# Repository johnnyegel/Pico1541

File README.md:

# Pico1541

A cycle-accurate Commodore 1541 disk drive emulator running on the Raspberry Pi Pico 2 (RP2350).

Unlike high-level IEC drive emulators (such as standard SD2IEC devices), **Pico1541** provides true hardware-level emulation. It models the MOS 6502 CPU and dual MOS 6522 VIAs in sub-cycle lockstep at 1 MHz, alongside a custom PIO-based magnetic track surface. As a result, Pico1541 is compatible with custom fastloaders, custom DOS routines, and sophisticated multi-stage copy protection schemes that execute code directly inside the drive.

---

## Table of Contents

- [Features](#features)
- [Emulation Status & Known Limitations](#emulation-status--known-limitations)
- [Architecture](#architecture)
- [Hardware & Pinout](#hardware--pinout)
- [ROM Installation & Legal Notice](#rom-installation--legal-notice)
  - [Compile-Time Embedding (Flash LittleFS)](#compile-time-embedding-flash-littlefs)
  - [Switching ROMs at Runtime (OLED Menu)](#switching-roms-at-runtime-oled-menu)
- [Prerequisites](#prerequisites)
- [Building & Flashing](#building--flashing)
  - [Building the Release Binary](#building-the-release-binary)
  - [Flashing via USB (BOOTSEL Mode)](#flashing-via-usb-bootsel-mode)
  - [Flashing via SWD Debugger](#flashing-via-swd-debugger)
- [Disk Image Conversion Tools (`nib2g64`)](#disk-image-conversion-tools-nib2g64)
- [Usage & Operation](#usage--operation)
  - [IEC Cable Connection](#iec-cable-connection)
  - [OLED Menu Navigation](#oled-menu-navigation)
  - [C64 Commands & Browser](#c64-commands--browser)
- [Repository Structure](#repository-structure)
- [Licensing](#licensing)

---

## Features

- **Cycle-Accurate Emulation Core:** Driven by `racc6502v4`, a dedicated micro-instruction 6502 CPU core executing in sub-cycle lockstep with dual 6522 VIAs at 1 MHz.
- **Fastloader & Protection Compatibility:** Compatible with popular fastloaders and custom drive code (Action Replay, Final Cartridge III, Epyx Fastload, Vorpal, V-MAX!, RapidLok, and custom track loaders).
- **Supported Disk Formats:**
  - **`.D64`**: Standard 35-track and 40-track Commodore disk images (dynamic on-the-fly GCR encoding/decoding).
  - **`.G64`**: Raw GCR track bitstreams with custom sector interleave and variable speed zones.
  - **`.PRG`**: Mount standalone PRG files as virtual single-file disks on the fly.
- **Weak-Bit (Unstable Flux) Emulation:** Dynamically mutates weak-bit areas (unstable GCR flux) across track revolutions using an LFSR pseudorandom generator without generating false SYNC markers, enabling copy-protected titles that rely on non-deterministic data (e.g. *Bruce Lee*, *Paperboy*) to load successfully.
- **Dual-Core Architecture (RP2350):**
  - **Core 1 (Emulator):** Dedicated entirely to the cycle-exact 6502 CPU, 6522 VIAs, and PIO magnetic surface streaming.
  - **Core 0 (Manager):** Runs asynchronous Embassy tasks managing the SD card, flash filesystem, OLED display, navigation buttons, and virtual directory synthesis.
- **Hardware PIO Magnetic Surface:** Utilizes RP2350 Programmable I/O (PIO) state machines and two-channel ping-pong DMA chaining for zero-CPU-overhead track data streaming to the emulated read head.
- **Storage Options:**
  - **MicroSD Card (FAT32):** Mount disk images directly from folders on your SD card.
  - **Internal Flash (LittleFS):** Built-in flash filesystem for bundled utilities, settings, and ROM storage.
- **On-Device Interface:**
  - 128x64 I2C SSD1306 OLED display.
  - 4-button tactile keypad (Up, Down, Select/Enter, Back/Exit).
  - RGB Status LED and Dual-color Drive Activity LED.
  - **Drive Sound Emulation:** Piezo speaker with PWM sample playback modeling authentic drive acoustics: motor hum with smooth acceleration/deceleration fade, head stepping clicks, and track 0 knocking sounds. Configurable volume (Muted, Low, Medium, High) and motor/stepper toggles saved in persistent flash.
- **SD2IEC Navigation & File Browser:** Intercepts `CD:` commands on IEC channel 15 to allow navigating SD card folders and disk images using standard Commodore 64 file browsers such as `fb64`.
- **Configurable Drive ID:** Switch drive device address between 8, 9, 10, or 11 with settings saved persistently in on-board flash.
- **Bundled Image Conversion Tools:** Includes standalone Rust CLI tools (`nib2g64` and `nbz2nib`) for converting raw `.NIB` and compressed `.NBZ` disk captures into standard `.G64` format with automatic seam detection, alignment, and weak-bit sanitization.

---

## Emulation Status & Known Limitations

Pico1541 actively strives for cycle-exact 1541 hardware behavior. However, full compatibility remains an ongoing development effort:

- **Cycle Accuracy Status:** While the micro-instruction 6502 core and dual 6522 VIA emulation pass instruction-level test suites and run most fastloaders, cycle-accurate behavior is **not yet 100% complete**. A small number of advanced demos utilizing extreme cycle-tight fastloaders do not yet load correctly.
- **Weak-Bit Support:** The magnetic surface engine includes weak-bit emulation for `.G64` images. Weak byte ranges (represented by `0x00` bytes in `.G64`) mutate pseudorandomly on each revolution without generating false SYNC pulses. This allows copy-protected games relying on weak bits (such as *Bruce Lee* and *Paperboy*) to pass protection checks and boot. Advanced multi-revolution density-drift protections may still behave unpredictably.
- **Disk Image Formats:** Native on-device emulation directly supports `.D64`, `.G64`, and `.PRG`. Raw `.NIB` format images cannot be processed directly on the microcontroller due to memory constraints; users can convert `.NIB` and `.NBZ` captures to `.G64` using the bundled `nib2g64` tool (see below) or external utilities prior to loading.

---

## Architecture

Pico1541 divides responsibilities cleanly across the RP2350's two Cortex-M33 cores:

```
┌────────────────────────────────────────┐  ┌────────────────────────────────────────┐
│         Core 0 — Drive Manager         │  │        Core 1 — Hardware Emulator      │
│  (Embassy Async / pico1541-manager)    │  │   (Cycle-Exact / pico1541-emulator)    │
├────────────────────────────────────────┤  ├────────────────────────────────────────┤
│ • MicroSD FAT32 Driver (SPI)           │  │ • 6502 CPU Core (racc6502v4) @ 1 MHz   │
│ • Internal Flash LittleFS Storage      │  │ • Dual 6522 VIAs (Timers, Handshake)   │
│ • D64 / G64 / PRG Handlers             │  │ • PIO Magnetic Surface Engine          │
│ • On-the-fly GCR Track Encoder         │  │ • Hardware DMA Ping-Pong Streaming     │
│ • SSD1306 OLED UI & Keypad Task       │  │ • Physical IEC Bus Line Polling        │
│ • SD2IEC CD: Command Interceptor       │  │ • Stepper Motor & Head Position Logic  │
└───────────────────┬────────────────────┘  └───────────────────┬────────────────────┘
                    │                                           │
                    └─────────── Shared Track Buffer ───────────┘
                                (Double-buffered GCR)
```

Communication between cores occurs via atomic flags and shared double-buffered track memory (`DualCoreTrackBuffer`), ensuring Core 1 never suffers jitter or interrupt latency from SD card I/O.

---

## Hardware & Pinout

Pico1541 interfaces with the 5V Commodore IEC bus using an open-collector inverter (7406 or 7405) with 1kΩ pull-up resistors on the 3.3V side. Ready-to-order KiCad PCB schematics and Gerbers are located in [`hardware/kicad/Pico1541v2/`](hardware/kicad/Pico1541v2/).

### Hardware Revision 2 (RP2350 / Raspberry Pi Pico 2)

| GPIO | Function | Description | Connection |
|:---:|:---|:---|:---|
| **GPIO 19** | `DATA_RX` | IEC Data In | Inverted from IEC Pin 5 (DATA, 1kΩ pull-up) |
| **GPIO 20** | `DATA_TX` | IEC Data Out | Drives 7406/7405 Open-Collector to IEC DATA |
| **GPIO 21** | `CLK_RX`  | IEC Clock In | Inverted from IEC Pin 4 (CLK, 1kΩ pull-up) |
| **GPIO 22** | `CLK_TX`  | IEC Clock Out | Drives 7406/7405 Open-Collector to IEC CLK |
| **GPIO 26** | `ATN_RX`  | IEC Attention In | Inverted from IEC Pin 3 (ATN, 1kΩ pull-up) |
| **GPIO 27** | `RESET_RX`| IEC Reset In | Inverted from IEC Pin 6 (RESET, 1kΩ pull-up) |
| **GPIO 4**  | `I2C0_SDA`| OLED Display SDA | SSD1306 I2C Data |
| **GPIO 5**  | `I2C0_SCL`| OLED Display SCL | SSD1306 I2C Clock |
| **GPIO 6..9**| `BUTTONS` | Tactile Buttons | Short to Ground (Up, Down, Enter, Back) |
| **GPIO 11** | `SD_DET`  | MicroSD Card Detect | SD Socket Card Detect Switch |
| **GPIO 12** | `SD_MISO` | MicroSD Data Out | SPI1 MISO (DAT0) |
| **GPIO 13** | `SD_CS`   | MicroSD Chip Select | SPI1 Chip Select (CD) |
| **GPIO 14** | `SD_CLK`  | MicroSD Clock | SPI1 SCK |
| **GPIO 15** | `SD_MOSI` | MicroSD Data In | SPI1 MOSI (CMD) |
| **GPIO 2**  | `PIEZO`   | Piezo Speaker | Head Stepper Sound Simulation |
| **GPIO 10** | `ACT_LED1`| Activity LED Pin 1 | Dual-color Activity Indicator |
| **GPIO 3**  | `ACT_LED2`| Activity LED Pin 2 | Dual-color Activity Indicator |
| **GPIO 16** | `RGB_RED` | Status RGB LED Red | Drive State Indicator |
| **GPIO 17** | `RGB_GREEN`| Status RGB LED Green | Drive State Indicator |
| **GPIO 18** | `RGB_BLUE`| Status RGB LED Blue | Drive State Indicator |

---

## ROM Installation & Legal Notice

> [!IMPORTANT]
> **Commodore DOS ROMs are proprietary and copyrighted.**
> This repository **does NOT contain any Commodore ROM files**.
> To use Pico1541, you must supply a legally obtained 16 KB (16,384 bytes) binary dump of a 1541 DOS ROM (such as `1541-II.251968-03.bin`, original `1541-c.bin`, or a licensed JiffyDOS 1541 ROM).

The ROM file must have an exact size of **16,384 bytes** (`0x4000` bytes).

### Compile-Time Embedding (Flash LittleFS)

This is the standard and recommended installation method. The build system packages the ROMs into an internal LittleFS flash partition on the Pico 2, making the drive completely self-contained.

1. Install `mklittlefs` on your system:
   - On Linux / macOS, build from source via [earlephilhower/mklittlefs](https://github.com/earlephilhower/mklittlefs) or install via your package manager.
   - Verify `mklittlefs` is accessible in your `PATH` (`mklittlefs --version`).
2. Copy your 16 KB ROM file(s) into the `flash-fs/roms/` directory in this repository:
   ```bash
   cp /path/to/1541-II.251968-03.bin flash-fs/roms/
   ```
   *(You can place multiple `.bin` or `.rom` files here—such as standard 1541-II DOS, 1541-C, and JiffyDOS—to switch between them on device).*
3. Compile the firmware as described in [Building & Flashing](#building--flashing). The build script (`build.rs`) will automatically pack `flash-fs/` into a LittleFS image (`fs.bin`) and link it into flash memory.

### Switching ROMs at Runtime (OLED Menu)

When multiple ROMs are bundled into the flash filesystem, you can switch between them on the fly:

1. On the device, navigate to:
   ```
   Main Menu -> Settings -> Select ROM
   ```
2. The OLED screen displays all ROMs discovered in internal storage.
3. Scroll to the desired ROM and press **Select**. The firmware immediately writes the selection to `/settings/boot_rom.txt` in persistent flash, reloads the emulator memory buffer, and resets the 6502 drive emulation.

---

## Prerequisites

### 1. Rust Toolchain

Pico1541 is built with Rust. Install the stable Rust toolchain via `rustup`:

```bash
curl --proto '=https' --tlsv1.2 -sSf https://sh.rustup.rs | sh
```

### 2. ARM Cortex-M Target

Add the bare-metal target for the RP2350 (Cortex-M33):

```bash
rustup target add thumbv8m.main-none-eabihf
```

### 3. Flashing Tools

Install `elf2uf2-rs` for easy USB drag-and-drop flashing (when the Pico 2 is in BOOTSEL mode):

```bash
cargo install elf2uf2-rs --locked
```

Alternatively, install [`picotool`](https://github.com/raspberrypi/picotool) or [`probe-rs`](https://probe.rs/) if you prefer flashing via SWD/JTAG debuggers.

---

## Building & Flashing

Clone the repository and enter the project directory:

```bash
git clone https://github.com/johnnyegel/Pico1541.git
cd Pico1541
```

Make sure you have placed your 16 KB DOS ROM in `flash-fs/roms/` before building.

### Building the Release Binary

Build the optimized release firmware:

```bash
cargo build -p pico1541-rp2350 --target thumbv8m.main-none-eabihf --release
```

### Flashing via USB (BOOTSEL Mode)

1. Unplug the Pico 2.
2. Hold down the **BOOTSEL** button on the Pico 2 board and plug it into your computer via USB.
3. Flash the binary:
   ```bash
   elf2uf2-rs -d target/thumbv8m.main-none-eabihf/release/pico1541-rp2350
   ```
   *(Or run `cargo run -p pico1541-rp2350 --release` directly from within the `crates/pico1541-rp2350` directory).*

### Flashing via SWD Debugger

If you are using a Raspberry Pi Debug Probe or SWD debugger with `probe-rs`, you can flash using:

```bash
cargo flash-swd
```

---

## Disk Image Conversion Tools (`nib2g64`)

While Pico1541's microcontroller firmware natively supports `.D64`, `.G64`, and `.PRG` formats, raw `.NIB` captures cannot be held entirely in the RP2350 RAM alongside the active emulation buffers. To make working with `.NIB` and `.NBZ` images seamless, Pico1541 includes host CLI conversion tools located in `tools/`:

- **Automatic Seam Detection & Alignment:** Detects track loop overlaps and aligns tracks to standard sector headers.
- **Weak-Bit Processing:** Identifies bad GCR runs and corrupt flux sequences, mapping them to weak-bit regions (`0x00`) so the firmware's magnetic surface engine can simulate non-deterministic flux at runtime.
- **Single File or Batch Processing:** Convert an individual image or point to a directory to batch-convert all `.nib` and `.nbz` files.

### Converting Images

```bash
# Convert a single .nib or .nbz to .g64
cargo run -p nib2g64 -- game.nib -o game.g64

# Batch convert an entire folder of disk images
cargo run -p nib2g64 -- /path/to/disks/
```

---

## Usage & Operation

### IEC Cable Connection

Connect a standard 6-pin DIN serial cable from the Commodore 64 / 128 serial port to the DIN connector on the Pico1541 hat. Ensure the ground reference is shared.

### OLED Menu Navigation

Pico1541 uses a 4-button navigation scheme:

- **Up / Down:** Scroll through menus, files, and disk directories.
- **Select / Enter:** Open a directory, mount a disk image (`.D64`, `.G64`), or mount a `.PRG`.
- **Back:** Navigate up one directory level, or unmount the current image and return to the main menu.
- **Fast Scroll:** Holding the Up or Down buttons skips through large lists quickly.

#### Menus Overview:
- **SD Card Browser:** Browse files and folders on your MicroSD card.
- **Internal Flash Browser:** Browse files stored on internal LittleFS flash storage (such as bundled utilities).
- **Settings:**
  - **Drive ID:** Configure device address between 8, 9, 10, or 11.
  - **Select ROM:** Choose which DOS ROM to load from internal flash.
  - **Sound Settings:** Configure volume (Muted, Low, Medium, High) and toggle motor hum or head-stepping sounds.
  - **Monitor:** Real-time bus and drive activity diagnostics display.

### C64 Commands & Browser

Once an image is mounted, use standard Commodore commands on your C64:

```basic
LOAD "$",8
LIST
LOAD "*",8,1
RUN
```

#### Navigating with C64 File Browsers (e.g., `fb64`):

Pico1541 includes built-in SD2IEC protocol command snooping. When using tools like `fb64`:
- Directory changes (`CD:DIRNAME`, `CD:_`, `CD:←`) are automatically intercepted on command channel 15.
- The virtual directory track is dynamically updated, allowing you to browse folders and mount disks directly from the C64 screen without touching the hardware buttons.

---

## Repository Structure

```
Pico1541/
├── crates/
│   ├── pico1541-emulator/     # Pure 6502 and dual 6522 VIA emulation engine
│   ├── racc6502v4/            # Cycle-accurate micro-step 6502 CPU implementation
│   ├── pico1541-manager/      # Async Embassy manager, disk formats, GCR, UI logic
│   ├── pico1541-rp-common/    # Shared hardware drivers (PIO, SPI, Display, Audio)
│   ├── pico1541-rp2350/       # Firmware entry point for Raspberry Pi Pico 2 (RP2350)
│   └── pico1541-common/       # Common definitions, events, and inter-core buffers
├── flash-fs/                  # Root filesystem packed into on-chip LittleFS partition
│   └── roms/                  # Location to place 16KB DOS ROMs for compile-time embedding
├── hardware/                  # KiCad schematics, PCB layouts, and Gerber files
│   └── kicad/
│       └── Pico1541v2/        # Hardware Revision 2 interface hat (RP2350)
├── tools/
│   ├── nib2g64/               # Standalone NIB/NBZ to G64 converter CLI tool
│   └── nbz2nib/               # Standalone NBZ decompressor CLI utility
├── scripts/                   # Tracing, logic analysis, and code generation scripts
├── COMMERCIAL_LICENSE.md      # Commercial manufacturing terms
└── LICENSE.md                 # Firmware license (PolyForm Noncommercial 1.0.0)
```

---

## Licensing

This project is made available under multiple licenses:

- **Firmware & Management Software:**
  Licensed under the **[PolyForm Noncommercial License 1.0.0](LICENSE.md)**. Free for personal, hobby, educational, and non-commercial use.
- **6502 Emulator Core (`racc6502v4`):**
  Licensed under the **[GNU General Public License v3.0 (GPL-3.0)](crates/racc6502v4/LICENSE.md)**.
- **Hardware Design & KiCad Schematics:**
  Licensed under the **[Creative Commons Attribution-NonCommercial 4.0 International (CC BY-NC 4.0)](hardware/LICENSE.md)**.
- **Commercial Licensing:**
  Commercial manufacturing and sale of assembled Pico1541 units requires a commercial license for a flat royalty fee of **5 EUR/USD per sold unit**. Please refer to [COMMERCIAL_LICENSE.md](COMMERCIAL_LICENSE.md) or contact [johnnyege@gmail.com](mailto:johnnyege@gmail.com) to arrange an agreement before starting production.

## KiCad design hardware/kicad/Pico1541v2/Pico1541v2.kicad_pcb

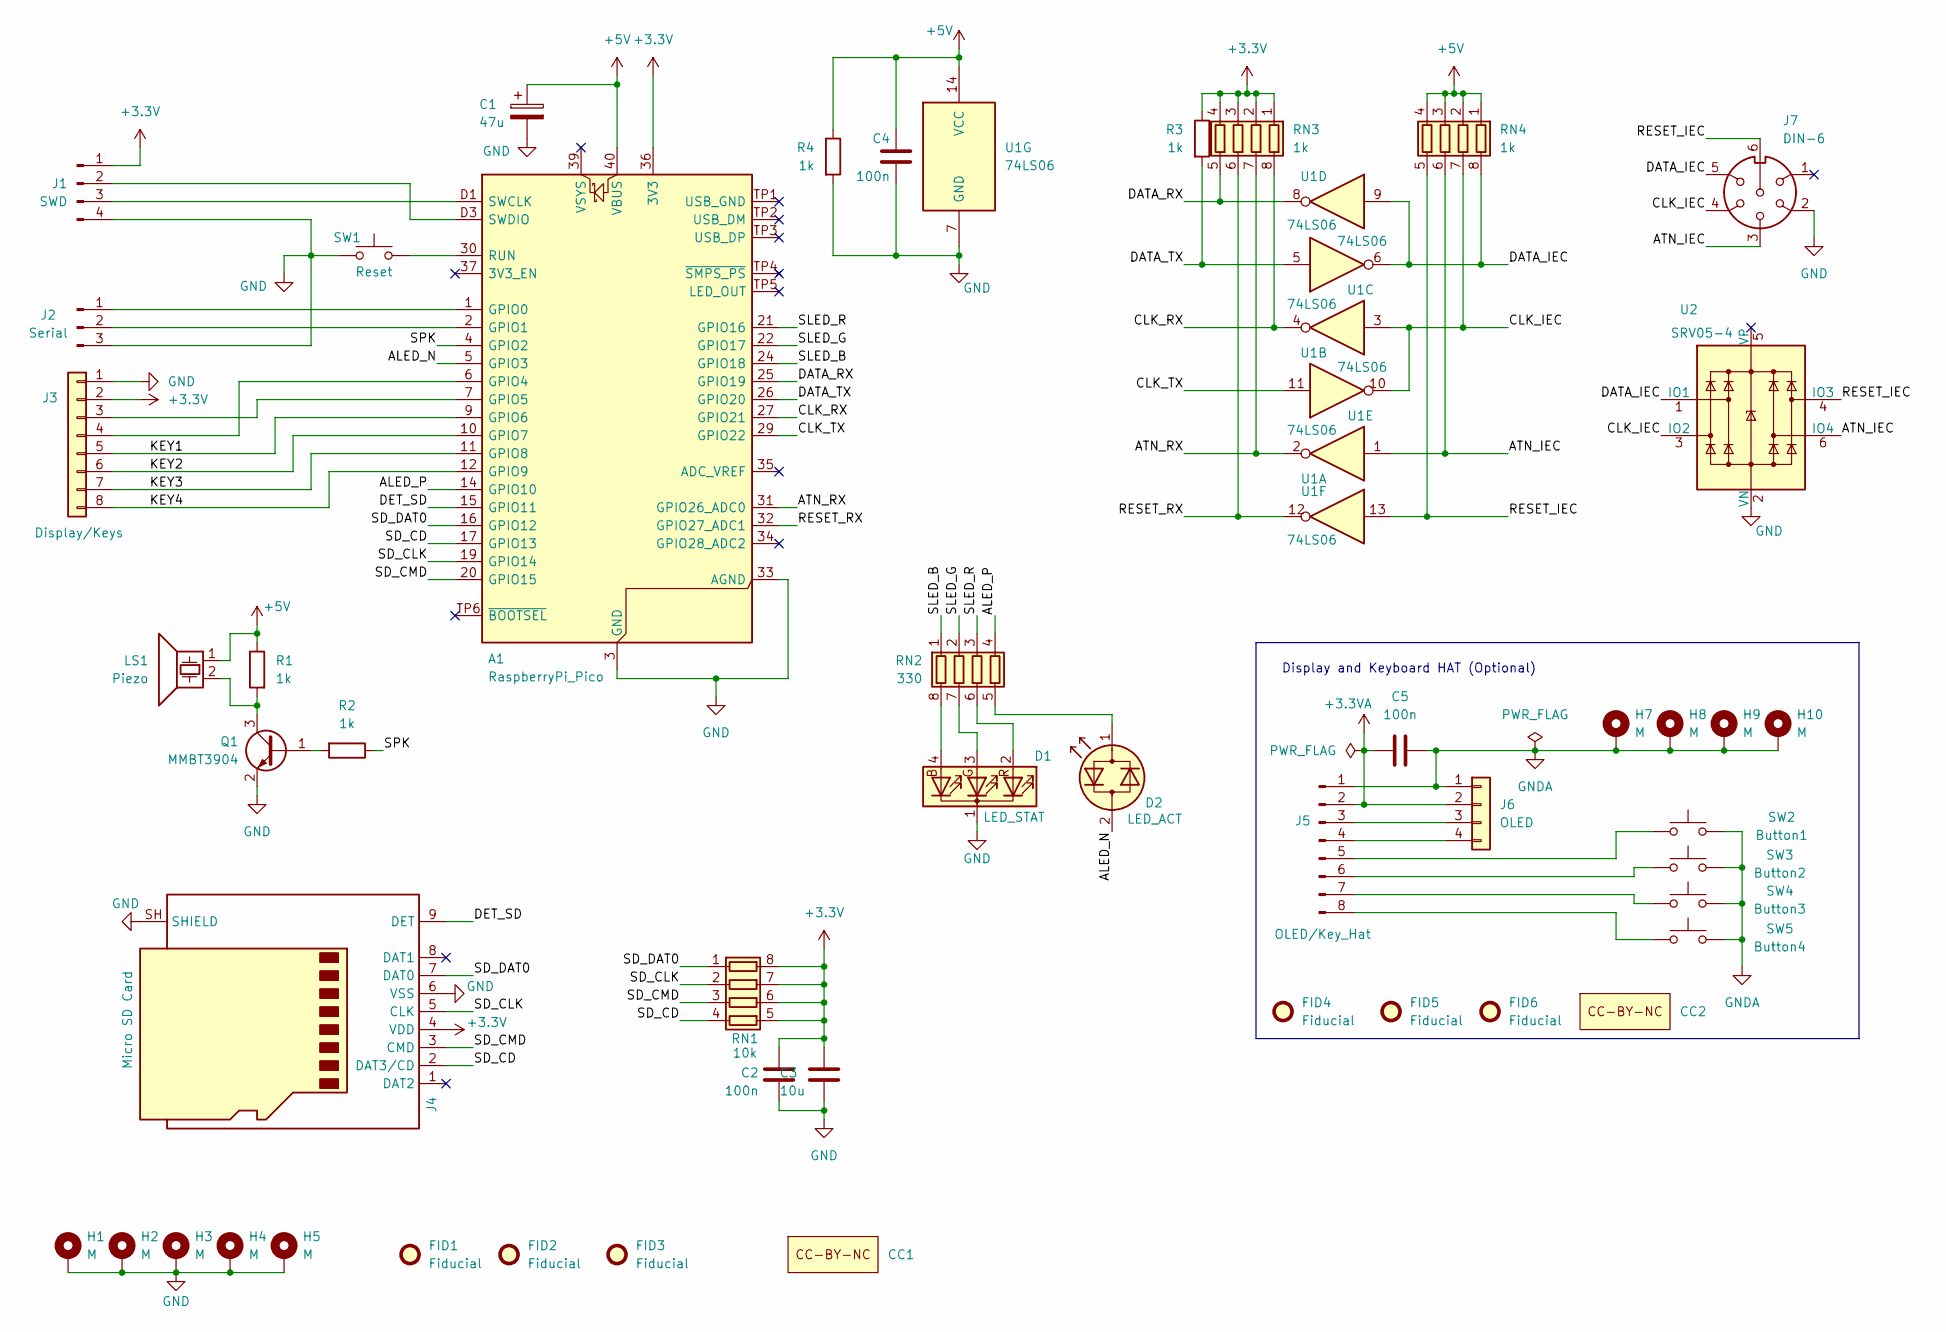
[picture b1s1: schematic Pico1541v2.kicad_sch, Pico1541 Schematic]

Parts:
A1: RaspberryPi_Pico; RaspberryPi_Pico_SMD
C1: 47u; CP_Elec_5x4.5
C2, C4, C5: 100n; C_0603_1608Metric_Pad1.08x0.95mm_HandSolder
C3: 10u; C_0603_1608Metric_Pad1.08x0.95mm_HandSolder
CC1, CC2: Symbol_CC-Noncommercial_CopperTop_Small
D1: LED_STAT; LED_D5.0mm-4_RGB_CorrectStaggered_Pins
D2: LED_ACT; LED_D5.0mm
FID1, FID2, FID3, FID4, FID5, FID6: Fiducial; Fiducial_1mm_Mask3mm
H1, H2, H3, H4, H5, H7, H8, H9, H10: M; MountingHole_2.5mm_Pad_Via
J1: SWD; PinHeader_1x04_P2.54mm_Vertical
J2: Serial; PinHeader_1x03_P2.54mm_Vertical
J3: Display/Keys; PinSocket_1x08_P2.54mm_Vertical
J4: Micro SD Card; MicroSD_HPJF
J5: OLED/Key_Hat; PinHeader_1x08_P2.54mm_Vertical
J6: OLED; PinSocket_1x04_P2.54mm_Vertical
J7: DIN-6; DIN-6-240deg
LS1: Piezo; PinSocket_1x02_P2.54mm_Vertical
Q1: MMBT3904; SOT-23
R1, R2, R3, R4: 1k; R_0603_1608Metric_Pad0.98x0.95mm_HandSolder
RN1: 10k; R_Array_Convex_4x0603
RN2: 330; R_Array_Convex_4x0603
RN3, RN4: 1k; R_Array_Convex_4x0603
SW1: Reset; SW_Tactile_SPST_Angled_PTS645Vx83-2LFS
SW2: Button1; SW_SPST_Omron_B3FS-100xP
SW3: Button2; SW_SPST_Omron_B3FS-100xP
SW4: Button3; SW_SPST_Omron_B3FS-100xP
SW5: Button4; SW_SPST_Omron_B3FS-100xP
U1: 74LS06; SO-14_3.9x8.65mm_P1.27mm
U2: SRV05-4; SOT-23-6

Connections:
+3.3V: A1.36 (3V3), C2.1, C3.1, J1.1, J3.2, J4.4 (VDD), R3.1, RN1.5 (R4.2), RN1.6 (R3.2), RN1.7 (R2.2), RN1.8 (R1.2), RN3.1 (R1.1), RN3.2 (R2.1), RN3.3 (R3.1), RN3.4 (R4.1)
+3.3VA: C5.1, J5.2, J6.2
+5V: A1.40 (VBUS), C1.1, C4.1, LS1.1, R1.1, R4.1, RN4.1 (R1.1), RN4.2 (R2.1), RN4.3 (R3.1), RN4.4 (R4.1), U1.14 (VCC)
/ALED_N: A1.5 (GPIO3), D2.2 (AK)
/ALED_P: A1.14 (GPIO10), RN2.4 (R4.1)
/ATN_IEC: J7.3, RN4.6 (R3.2), U1.1, U2.6 (IO4)
/ATN_RX: A1.31 (GPIO26_ADC0), RN3.7 (R2.2), U1.2
/CLK_IEC: J7.4, RN4.7 (R2.2), U1.3, U1.10, U2.3 (IO2)
/CLK_RX: A1.27 (GPIO21), RN3.8 (R1.2), U1.4
/CLK_TX: A1.29 (GPIO22), U1.11
/DATA_IEC: J7.5, RN4.8 (R1.2), U1.6, U1.9, U2.1 (IO1)
/DATA_RX: A1.25 (GPIO19), RN3.5 (R4.2), U1.8
/DATA_TX: A1.26 (GPIO20), R3.2, U1.5
/DET_SD: A1.15 (GPIO11), J4.9 (DET)
/KEY1: A1.9 (GPIO6), J3.5
/KEY2: A1.10 (GPIO7), J3.6
/KEY3: A1.11 (GPIO8), J3.7
/KEY4: A1.12 (GPIO9), J3.8
/RESET_IEC: J7.6, RN4.5 (R4.2), U1.13, U2.4 (IO3)
/RESET_RX: A1.32 (GPIO27_ADC1), RN3.6 (R3.2), U1.12
/SD_CD: A1.17 (GPIO13), J4.2 (DAT3/CD), RN1.4 (R4.1)
/SD_CLK: A1.19 (GPIO14), J4.5 (CLK), RN1.2 (R2.1)
/SD_CMD: A1.20 (GPIO15), J4.3 (CMD), RN1.3 (R3.1)
/SD_DAT0: A1.16 (GPIO12), J4.7 (DAT0), RN1.1 (R1.1)
/SLED_B: A1.24 (GPIO18), RN2.1 (R1.1)
/SLED_G: A1.22 (GPIO17), RN2.2 (R2.1)
/SLED_R: A1.21 (GPIO16), RN2.3 (R3.1)
/SPK: A1.4 (GPIO2), R2.1
GND: A1.3 (GND), A1.8 (GND), A1.13 (GND), A1.18 (GND), A1.23 (GND), A1.28 (GND), A1.33 (AGND), A1.38 (GND), A1.D2 (GND), C1.2, C2.2, C3.2, C4.2, D1.1 (K), H1.1 (1_1), H2.1 (1_1), H3.1 (1_1), H4.1 (1_1), H5.1 (1_1), J1.4, J2.3, J3.1, J4.6 (VSS), J4.SH (SHIELD), J7.2, Q1.2 (E), R4.2, SW1.1, U1.7 (GND), U2.2 (VN)
GNDA: C5.2, H7.1 (1_1), H8.1 (1_1), H9.1 (1_1), H10.1 (1_1), J5.1, J6.1, SW2.2, SW3.2, SW4.2, SW5.2
unnamed: A1.1 (GPIO0), J2.1
unnamed: A1.2 (GPIO1), J2.2
unnamed: A1.6 (GPIO4), J3.4
unnamed: A1.7 (GPIO5), J3.3
unnamed: A1.30 (RUN), SW1.2
unnamed: A1.D1 (SWCLK), J1.3
unnamed: A1.D3 (SWDIO), J1.2
unnamed: D1.4 (BA), RN2.8 (R1.2)
unnamed: D1.3 (GA), RN2.7 (R2.2)
unnamed: D1.2 (RA), RN2.6 (R3.2)
unnamed: D2.1 (KA), RN2.5 (R4.2)
unnamed: J5.3, J6.3
unnamed: J5.4, J6.4
unnamed: J5.5, SW2.1
unnamed: J5.6, SW3.1
unnamed: J5.7, SW4.1
unnamed: J5.8, SW5.1
unnamed: Q1.1 (B), R2.2
unnamed: LS1.2, Q1.3 (C), R1.2

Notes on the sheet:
Display and Keyboard HAT (Optional)

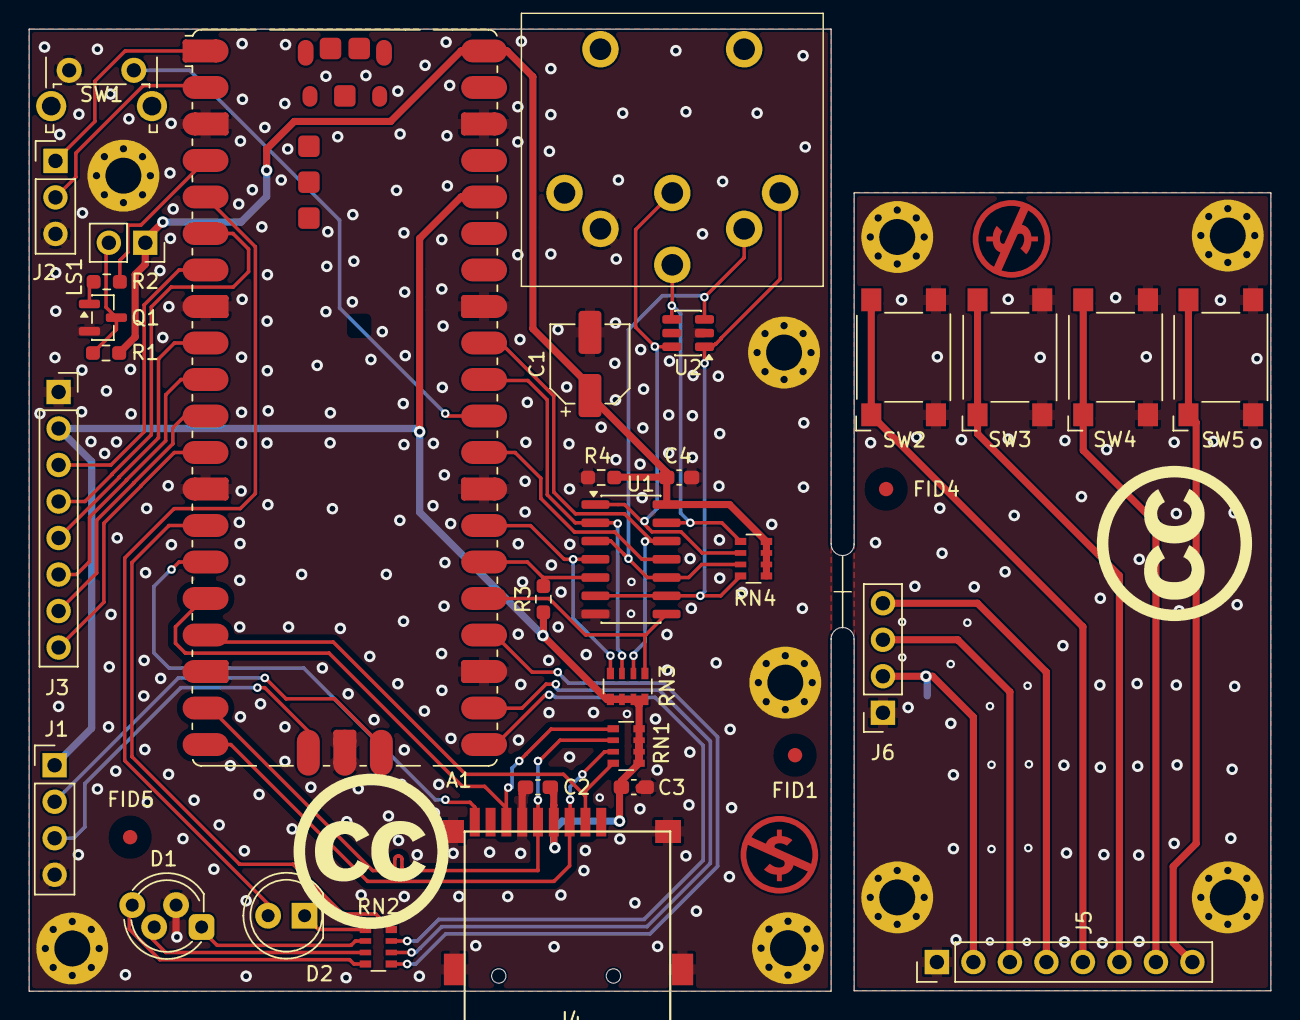
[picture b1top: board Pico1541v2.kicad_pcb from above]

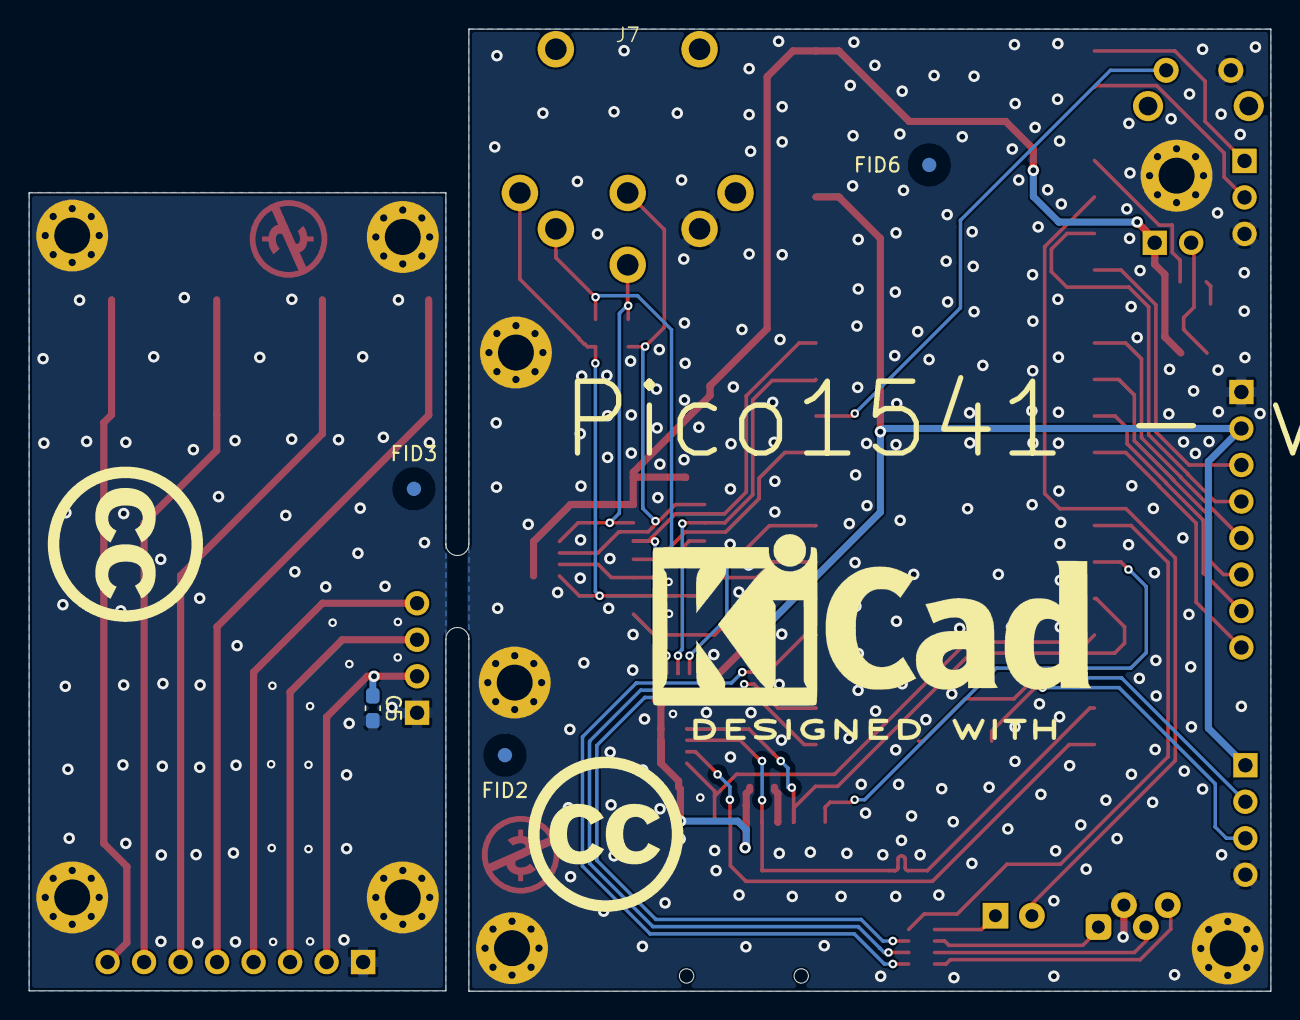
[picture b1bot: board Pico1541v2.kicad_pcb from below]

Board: 2 copper layers, 86.4 x 66.9 mm, 49 parts (4 on the bottom side), 49 nets.

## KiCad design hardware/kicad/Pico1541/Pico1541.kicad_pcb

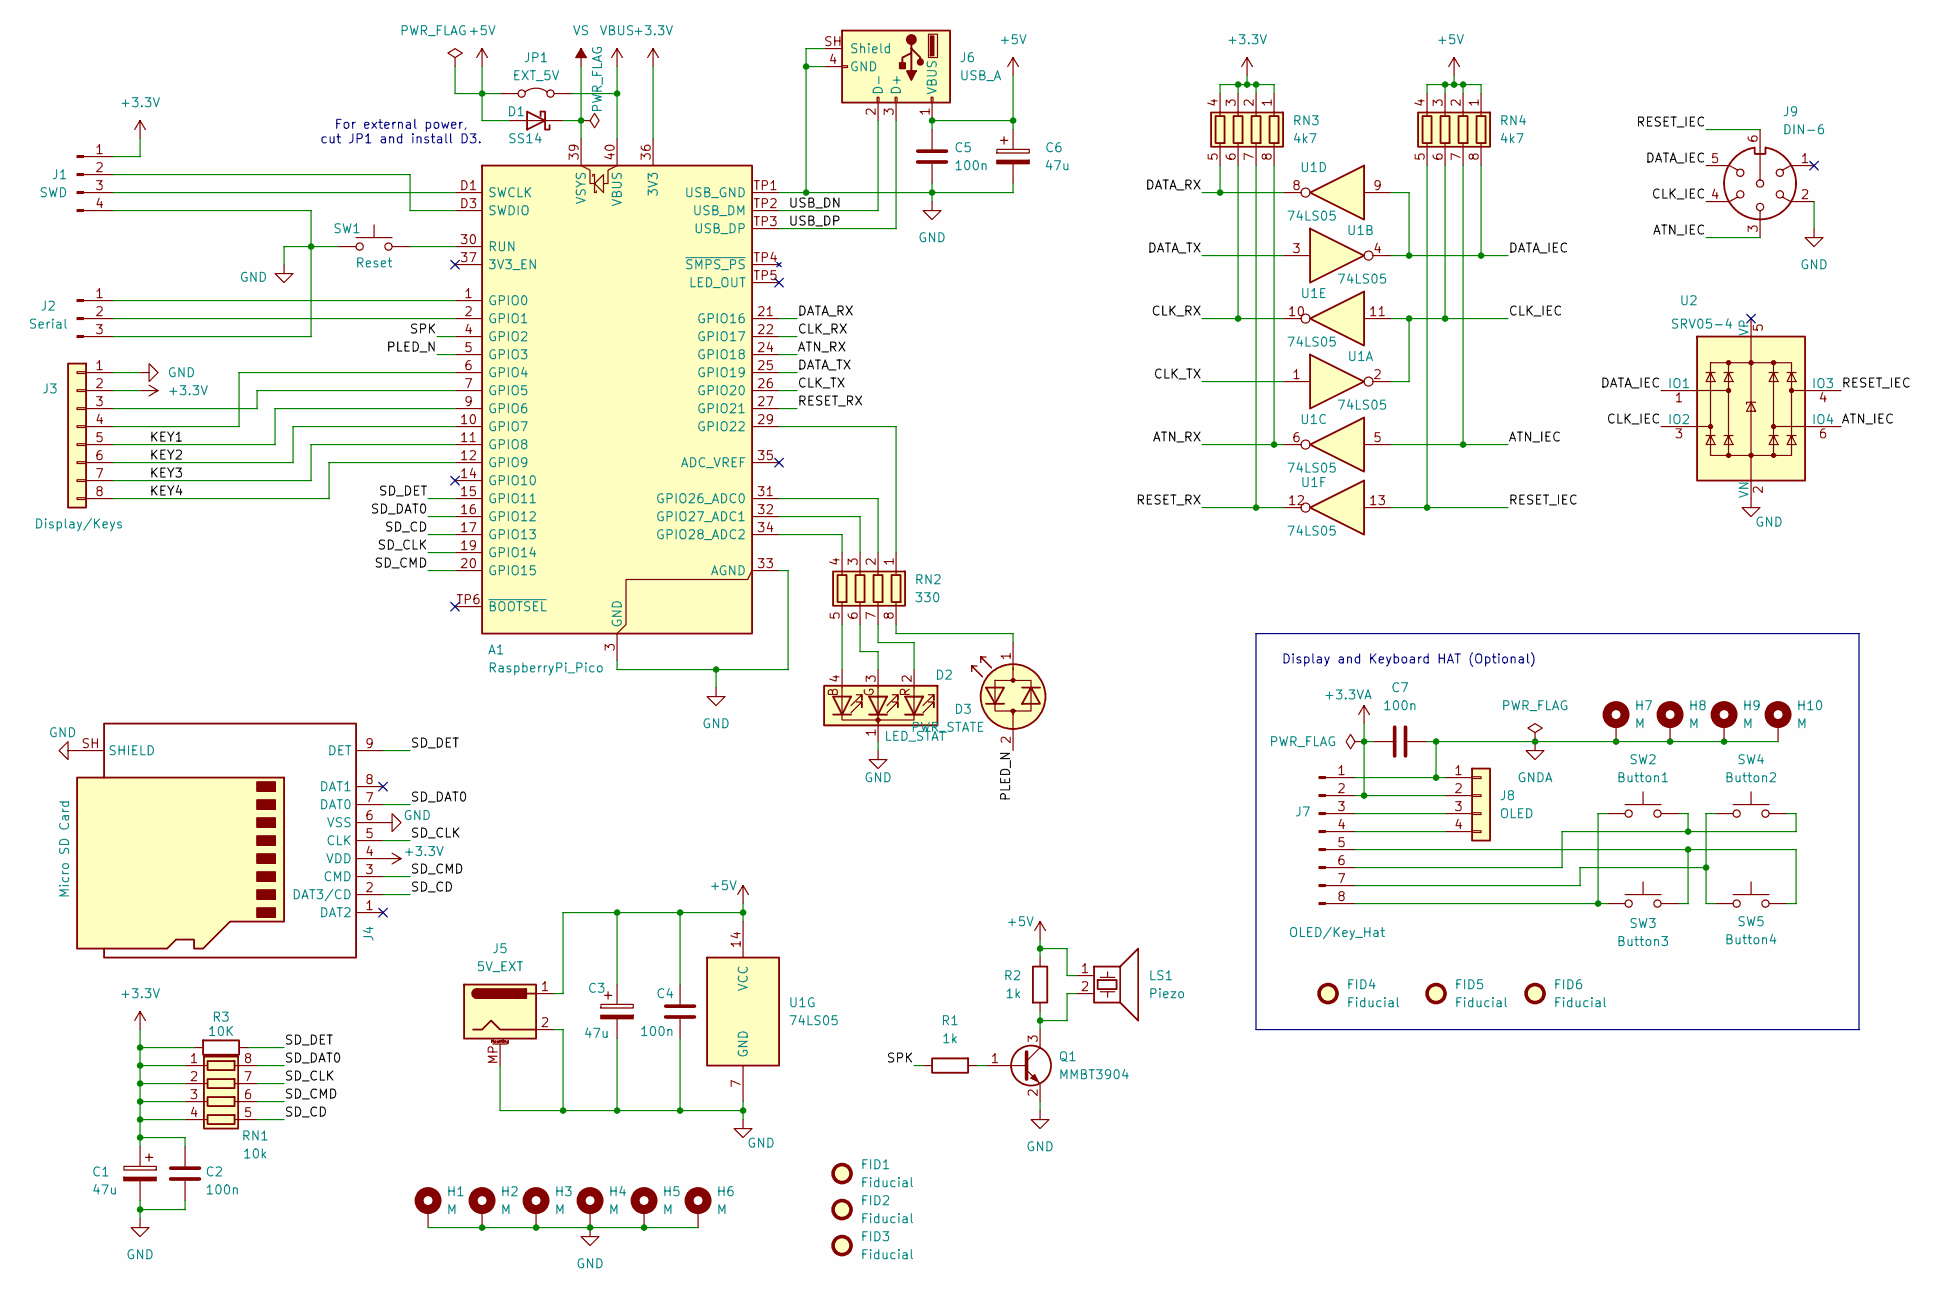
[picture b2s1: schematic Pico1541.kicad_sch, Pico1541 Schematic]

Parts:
A1: RaspberryPi_Pico; RaspberryPi_Pico_SMD
C1, C3, C6: 47u; CP_Elec_5x5.4
C2, C4, C5, C7: 100n; C_0603_1608Metric_Pad1.08x0.95mm_HandSolder
D1: SS14; D_SMA
D2: LED_STAT; LED_D5.0mm-4_RGB_CorrectStaggered_Pins
D3: PWR_STATE; LED_D5.0mm
FID1, FID2, FID3, FID4, FID5, FID6: Fiducial; Fiducial_1mm_Mask3mm
H1, H2, H3, H4, H5, H6, H7, H8, H9, H10: M; MountingHole_2.5mm_Pad_Via
J1: SWD; PinHeader_1x04_P2.54mm_Vertical
J2: Serial; PinHeader_1x03_P2.54mm_Vertical
J3: Display/Keys; PinSocket_1x08_P2.54mm_Vertical
J4: Micro SD Card; MicroSD_HPJF
J5: 5V_EXT; BarrelJack_CUI_PJ-063AH_Horizontal_CircularHoles
J6: USB_A; USB_A_Connfly_DS1095
J7: OLED/Key_Hat; PinHeader_1x08_P2.54mm_Vertical
J8: OLED; PinSocket_1x04_P2.54mm_Vertical
J9: DIN-6; DIN-6-240deg
JP1: EXT_5V; SolderJumper-2_P1.3mm_Bridged_RoundedPad1.0x1.5mm
LS1: Piezo; PinSocket_1x02_P2.54mm_Vertical
Q1: MMBT3904; SOT-23
R1, R2: 1k; R_0603_1608Metric_Pad0.98x0.95mm_HandSolder
R3: 10K; R_0603_1608Metric_Pad0.98x0.95mm_HandSolder
RN1: 10k; R_Array_Convex_4x0603
RN2: 330; R_Array_Convex_4x0603
RN3, RN4: 4k7; R_Array_Convex_4x0603
SW1: Reset; SW_Tactile_SPST_Angled_PTS645Vx83-2LFS
SW2: Button1; SW_SPST_EVPBF
SW3: Button3; SW_SPST_EVPBF
SW4: Button2; SW_SPST_EVPBF
SW5: Button4; SW_SPST_EVPBF
U1: 74LS05; SO-14_3.9x8.65mm_P1.27mm
U2: SRV05-4; SOT-23-6

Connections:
+3.3V: A1.36 (3V3), C1.1, C2.1, J1.1, J3.2, J4.4 (VDD), R3.2, RN1.1 (R1.1), RN1.2 (R2.1), RN1.3 (R3.1), RN1.4 (R4.1), RN3.1 (R1.1), RN3.2 (R2.1), RN3.3 (R3.1), RN3.4 (R4.1)
+3.3VA: C7.1, J7.2, J8.2
+5V: C3.1, C4.1, C5.1, C6.1, D1.2 (A), J5.1, J6.1 (VBUS), JP1.1 (A), LS1.1, R2.1, RN4.1 (R1.1), RN4.2 (R2.1), RN4.3 (R3.1), RN4.4 (R4.1), U1.14 (VCC)
/ATN_IEC: J9.3, RN4.7 (R2.2), U1.5, U2.6 (IO4)
/ATN_RX: A1.24 (GPIO18), RN3.8 (R1.2), U1.6
/CLK_IEC: J9.4, RN4.6 (R3.2), U1.2, U1.11, U2.3 (IO2)
/CLK_RX: A1.22 (GPIO17), RN3.6 (R3.2), U1.10
/CLK_TX: A1.26 (GPIO20), U1.1
/DATA_IEC: J9.5, RN4.8 (R1.2), U1.4, U1.9, U2.1 (IO1)
/DATA_RX: A1.21 (GPIO16), RN3.5 (R4.2), U1.8
/DATA_TX: A1.25 (GPIO19), U1.3
/KEY1: A1.9 (GPIO6), J3.5
/KEY2: A1.10 (GPIO7), J3.6
/KEY3: A1.11 (GPIO8), J3.7
/KEY4: A1.12 (GPIO9), J3.8
/PLED_N: A1.5 (GPIO3), D3.2 (AK)
/RESET_IEC: J9.6, RN4.5 (R4.2), U1.13, U2.4 (IO3)
/RESET_RX: A1.27 (GPIO21), RN3.7 (R2.2), U1.12
/SD_CD: A1.17 (GPIO13), J4.2 (DAT3/CD), RN1.5 (R4.2)
/SD_CLK: A1.19 (GPIO14), J4.5 (CLK), RN1.7 (R2.2)
/SD_CMD: A1.20 (GPIO15), J4.3 (CMD), RN1.6 (R3.2)
/SD_DAT0: A1.16 (GPIO12), J4.7 (DAT0), RN1.8 (R1.2)
/SD_DET: A1.15 (GPIO11), J4.9 (DET), R3.1
/SPK: A1.4 (GPIO2), R1.1
/USB_DN: A1.TP2 (USB_DM), J6.2 (D-)
/USB_DP: A1.TP3 (USB_DP), J6.3 (D+)
GND: A1.3 (GND), A1.8 (GND), A1.13 (GND), A1.18 (GND), A1.23 (GND), A1.28 (GND), A1.33 (AGND), A1.38 (GND), A1.D2 (GND), A1.TP1 (USB_GND), C1.2, C2.2, C3.2, C4.2, C5.2, C6.2, D2.1 (K), H1.1 (1_1), H2.1 (1_1), H3.1 (1_1), H4.1 (1_1), H5.1 (1_1), H6.1 (1_1), J1.4, J2.3, J3.1, J4.6 (VSS), J4.SH (SHIELD), J5.2, J5.MP (MountPin_MP), J6.4 (GND), J6.SH (Shield), J9.2, Q1.2 (E), SW1.1, U1.7 (GND), U2.2 (VN)
GNDA: C7.2, H7.1 (1_1), H8.1 (1_1), H9.1 (1_1), H10.1 (1_1), J7.1, J8.1
unnamed: A1.1 (GPIO0), J2.1
unnamed: A1.2 (GPIO1), J2.2
unnamed: A1.6 (GPIO4), J3.4
unnamed: A1.7 (GPIO5), J3.3
unnamed: A1.29 (GPIO22), RN2.1 (R1.1)
unnamed: A1.31 (GPIO26_ADC0), RN2.2 (R2.1)
unnamed: A1.32 (GPIO27_ADC1), RN2.3 (R3.1)
unnamed: A1.34 (GPIO28_ADC2), RN2.4 (R4.1)
unnamed: A1.30 (RUN), SW1.2
unnamed: A1.D1 (SWCLK), J1.3
unnamed: A1.D3 (SWDIO), J1.2
unnamed: D2.4 (BA), RN2.5 (R4.2)
unnamed: D2.3 (GA), RN2.6 (R3.2)
unnamed: D2.2 (RA), RN2.7 (R2.2)
unnamed: D3.1 (KA), RN2.8 (R1.2)
unnamed: J7.3, J8.3
unnamed: J7.4, J8.4
unnamed: J7.5, SW3.2, SW5.2
unnamed: J7.6, SW2.2, SW4.2
unnamed: J7.7, SW4.1, SW5.1
unnamed: J7.8, SW2.1, SW3.1
unnamed: Q1.1 (B), R1.2
unnamed: LS1.2, Q1.3 (C), R2.2
VBUS: A1.40 (VBUS), JP1.2 (B)
VS: A1.39 (VSYS), D1.1 (K)

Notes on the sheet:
For external power, cut JP1 and install D3.
Display and Keyboard HAT (Optional)

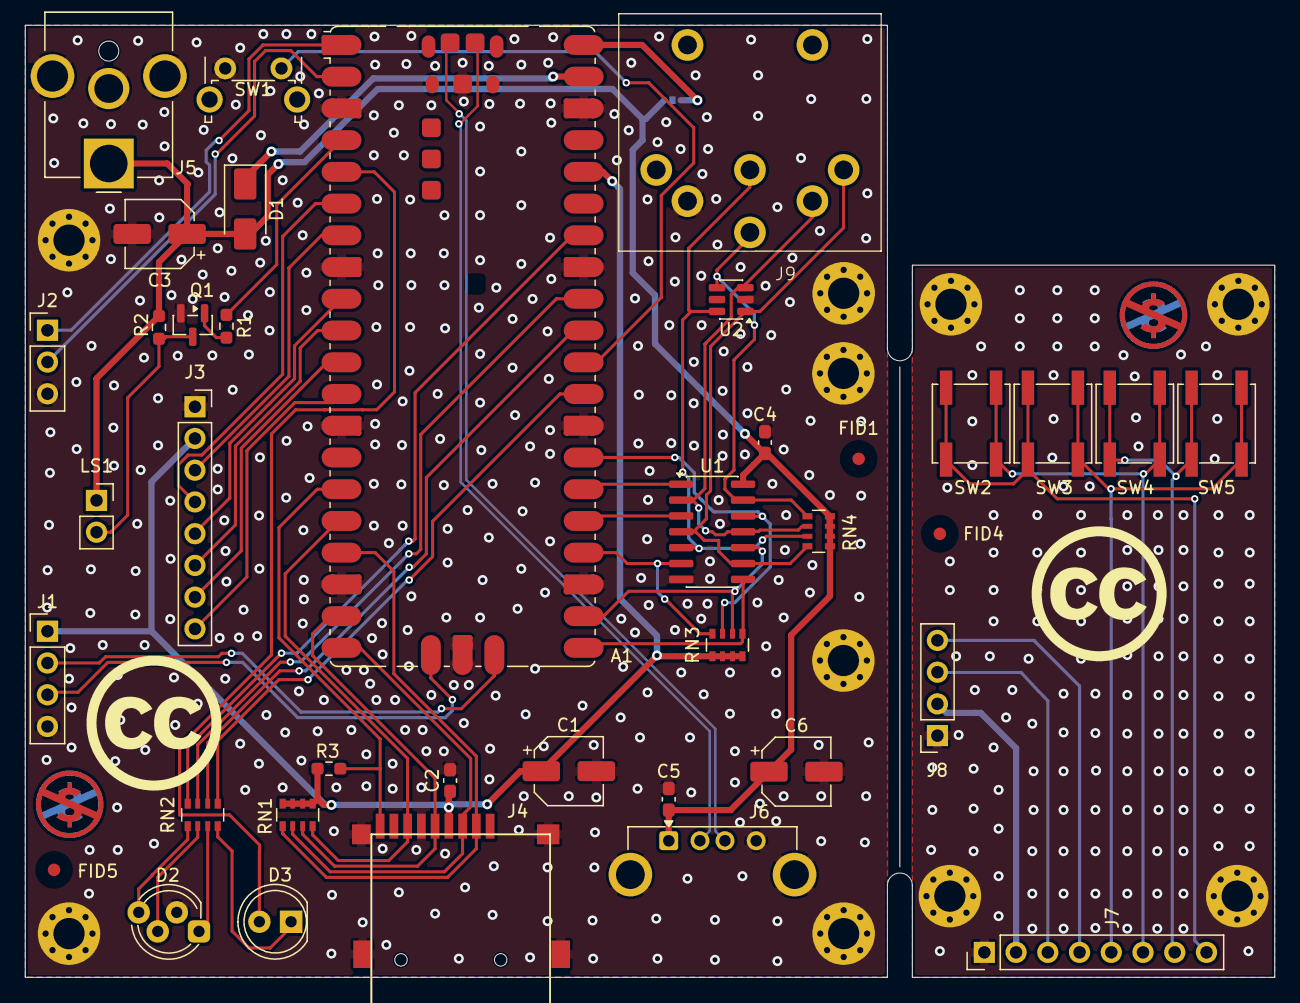
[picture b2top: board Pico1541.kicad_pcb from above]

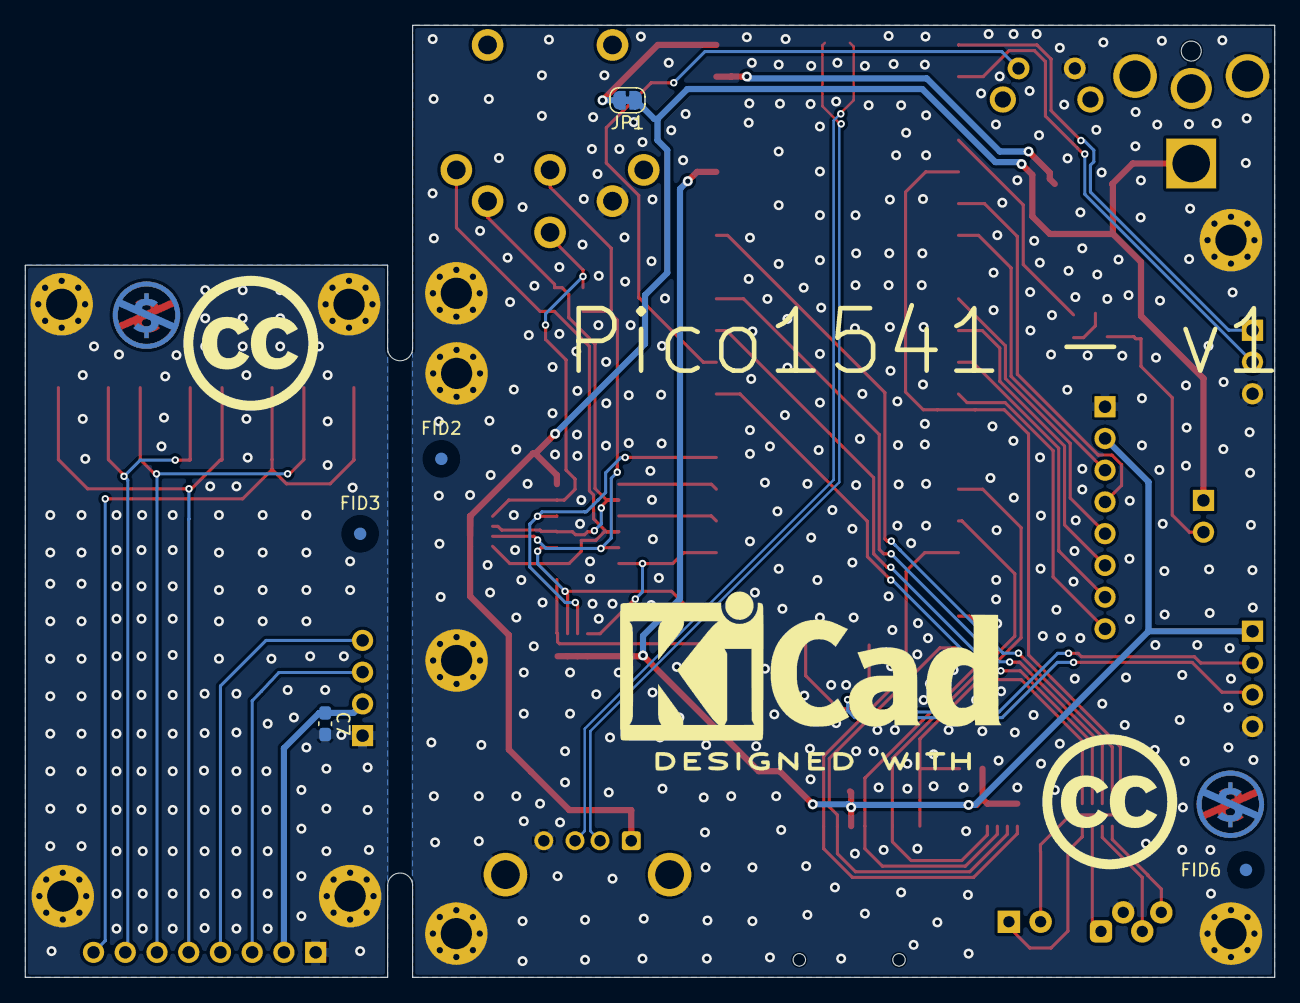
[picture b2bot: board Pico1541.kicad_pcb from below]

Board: 2 copper layers, 100.0 x 76.2 mm, 53 parts (5 on the bottom side), 53 nets.
